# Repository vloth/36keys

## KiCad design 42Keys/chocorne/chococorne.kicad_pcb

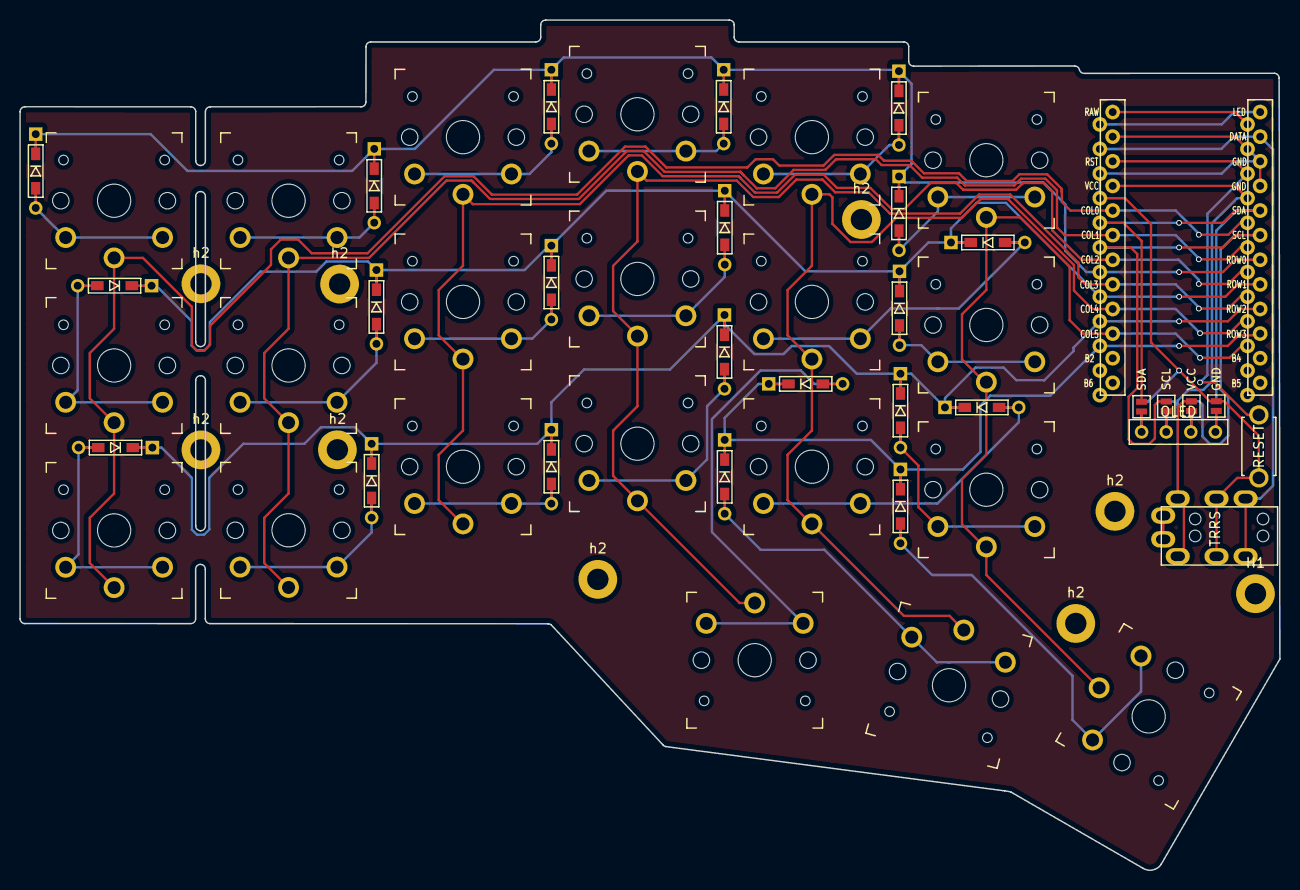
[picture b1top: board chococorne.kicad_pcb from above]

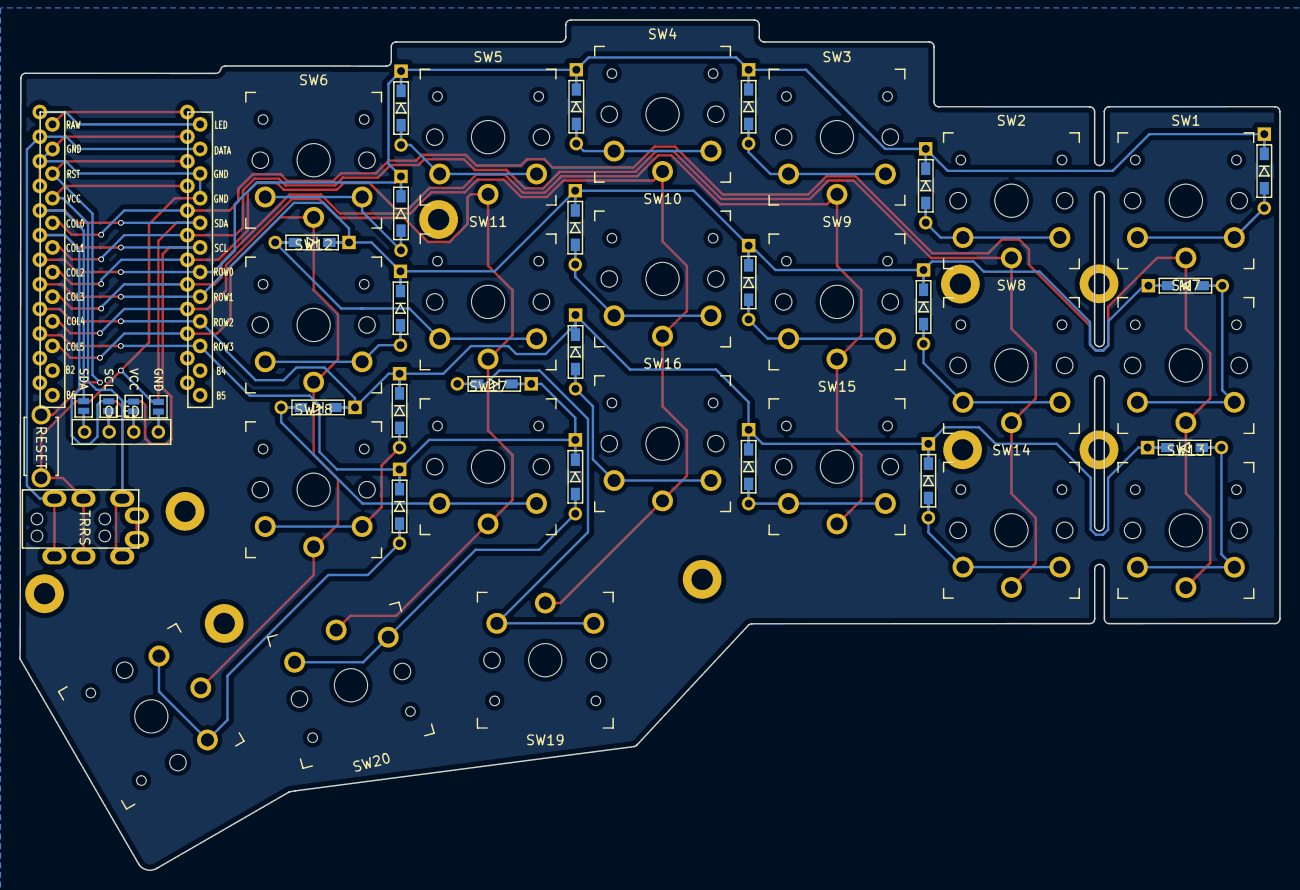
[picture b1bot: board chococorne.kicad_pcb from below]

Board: 2 copper layers, 130.0 x 87.7 mm, 63 parts (4 on the bottom side), 41 nets.

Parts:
D1, D2, D3, D4, D5, D6, D7, D8, D9, D10, D11, D12, D13, D14, D15, D16, D17, D18, D19, D20, D21: D; D3_TH_SMD
H1: h1; LEGO_HOLE
J1: MJ-4PP-9
J2: OLED
JP6, JP61: SDA; Jumper
JP62, JP68: GND; Jumper
JP63, JP66: SCL; Jumper
JP64, JP65: VCC; Jumper
RSW1: Val**; ResetSW
SW1, SW2, SW3, SW4, SW5, SW6, SW7, SW8, SW9, SW10, SW11, SW12, SW13, SW14, SW15, SW16, SW17, SW18, SW19, SW20: SW_PUSH; SW_PG1350_reversible_b2
SW21: SW_PUSH; SW_PG1350_15_reversible_b2
U1: ProMicro; ProMicro_v2
h2, h2#2, h2#3, h2#4, h2#5, h2#6, h2#7, h2#8: h2; LEGO_HOLE

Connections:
GND: J1.C, JP62.1, JP68.1, RSW1.1, U1.3, U1.4, U1.23
unnamed: D1.2, SW1.2
unnamed: D2.2, SW2.2
unnamed: D3.2, SW3.2
unnamed: D4.2, SW4.2
unnamed: D5.2, SW5.2
unnamed: D6.2, SW6.2
unnamed: D7.2, SW7.2
unnamed: D8.2, SW8.2
unnamed: D9.2, SW9.2
unnamed: D10.2, SW10.2
unnamed: D11.2, SW11.2
unnamed: D12.2, SW12.2
unnamed: D13.2, SW13.2
unnamed: D14.2, SW14.2
unnamed: D15.2, SW15.2
unnamed: D16.2, SW16.2
unnamed: D17.2, SW17.2
unnamed: D18.2, SW18.2
unnamed: D19.2, SW19.2
unnamed: D20.2, SW20.2
unnamed: D21.2, SW21.2
unnamed: J2.3, JP65.2, JP66.2
unnamed: J2.4, JP6.2, JP68.2
unnamed: J2.2, JP63.2, JP64.2
unnamed: J2.1, JP61.2, JP62.2
SCL: JP63.1, JP66.1, U1.6
SDA: JP6.1, JP61.1, U1.5
VCC: J1.D, JP64.1, JP65.1, U1.21
col0: SW1.1, SW7.1, SW13.1, U1.20
col1: SW2.1, SW8.1, SW14.1, U1.19
col2: SW3.1, SW9.1, SW15.1, U1.18
col3: SW4.1, SW10.1, SW16.1, SW19.1, U1.17
col4: SW5.1, SW11.1, SW17.1, SW20.1, U1.16
col5: SW6.1, SW12.1, SW18.1, SW21.1, U1.15
data: J1.B, U1.2
reset: RSW1.2, U1.22
row0: D1.1, D2.1, D3.1, D4.1, D5.1, D6.1, U1.7
row1: D7.1, D8.1, D9.1, D10.1, D11.1, D12.1, U1.8
row2: D13.1, D14.1, D15.1, D16.1, D17.1, D18.1, U1.9
row3: D19.1, D20.1, D21.1, U1.10

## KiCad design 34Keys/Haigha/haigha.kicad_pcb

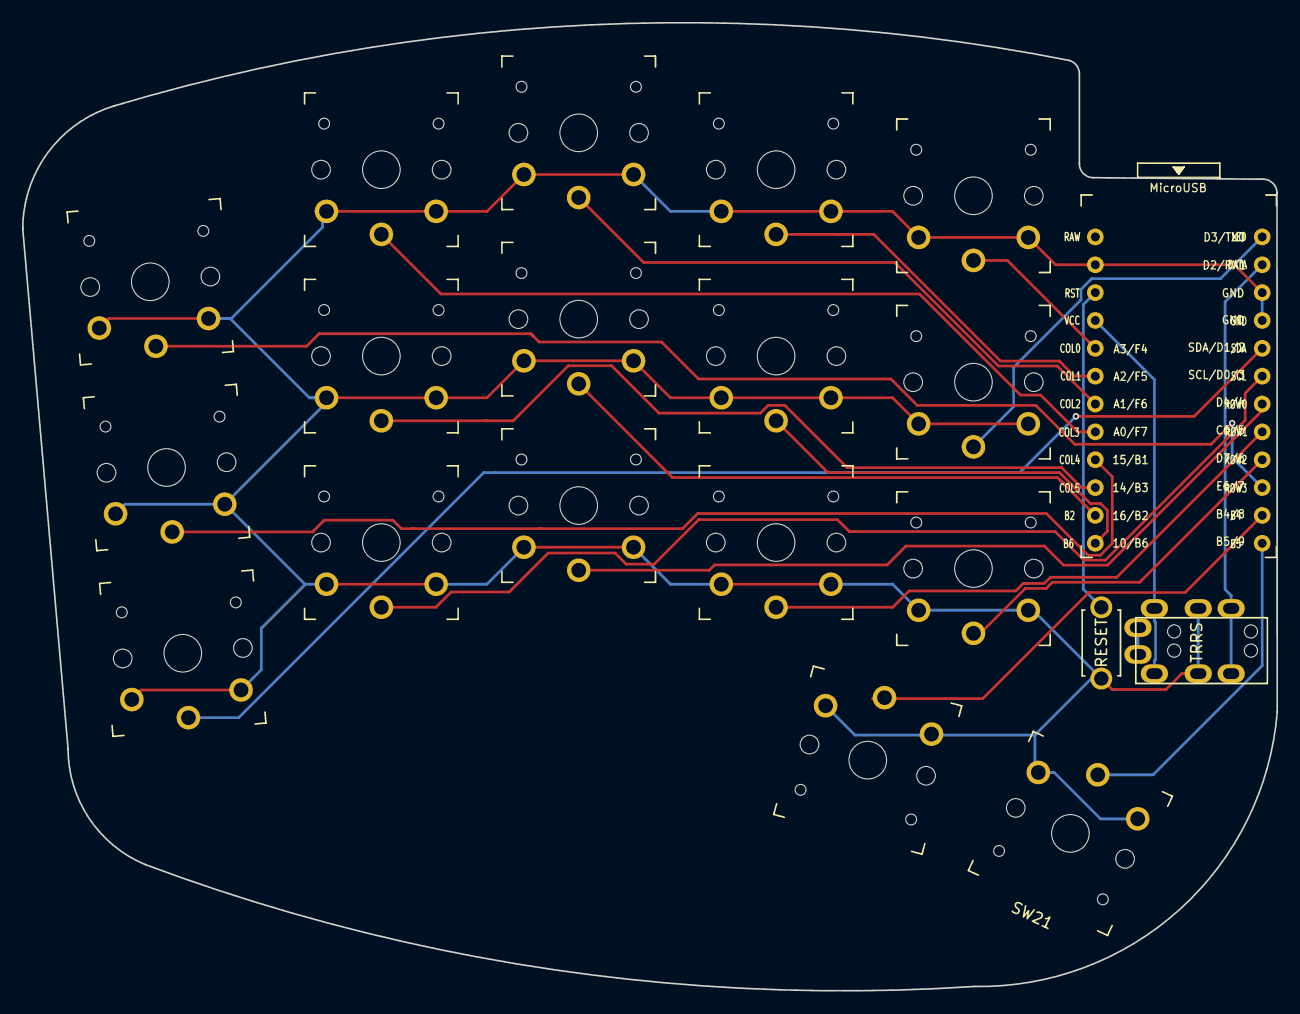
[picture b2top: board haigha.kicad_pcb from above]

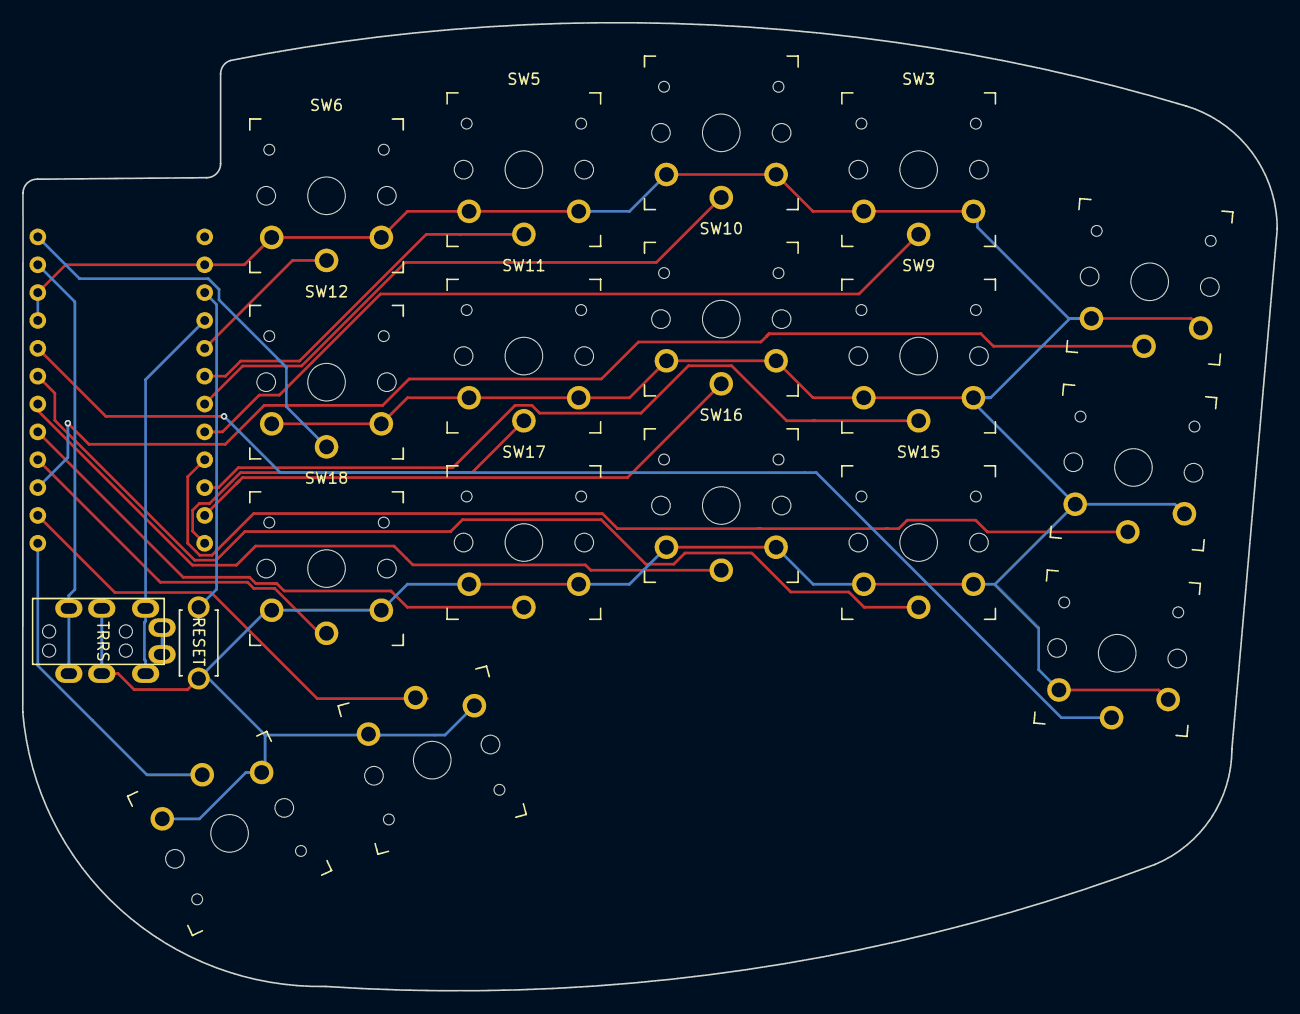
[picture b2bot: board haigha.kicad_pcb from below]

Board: 2 copper layers, 114.4 x 88.3 mm, 20 parts (2 on the bottom side), 21 nets.

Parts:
J1: MJ-4PP-9
RSW1: Val**; ResetSW
SW2, SW3, SW4, SW5, SW6, SW8, SW9, SW10, SW11, SW12, SW14, SW15, SW16, SW17, SW18, SW20, SW21: SW_PUSH; SW_PG1350_reversible_b2
U1: ProMicro; ProMicro_v3

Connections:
GND: J1.C, RSW1.2, SW2.2, SW3.2, SW4.2, SW5.2, SW6.2, SW8.2, SW9.2, SW10.2, SW11.2, SW12.2, SW14.2, SW15.2, SW16.2, SW17.2, SW18.2, SW20.2, SW21.2, U1.3, U1.4, U1.23
LED: SW12.1, U1.1
unnamed: SW6.1, U1.20
unnamed: SW20.1, U1.11
unnamed: SW21.1, U1.12
unnamed: SW11.1, U1.13
unnamed: SW10.1, U1.14
SCL: SW15.1, U1.6
SDA: SW14.1, U1.5
VCC: J1.D, U1.21
col1: SW5.1, U1.19
col2: SW4.1, U1.18
col3: SW3.1, U1.17
col4: SW8.1, U1.16
col5: SW9.1, U1.15
data: J1.B, U1.2
reset: RSW1.1, U1.22
row0: SW16.1, U1.7
row1: SW17.1, U1.8
row2: SW18.1, U1.9
row3: SW2.1, U1.10

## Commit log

2020-11-30 Increse drill hole size for chocorne and reroute
2020-11-30 Increase drill holes by ~6%
2020-11-30 Re route haigha tracks
